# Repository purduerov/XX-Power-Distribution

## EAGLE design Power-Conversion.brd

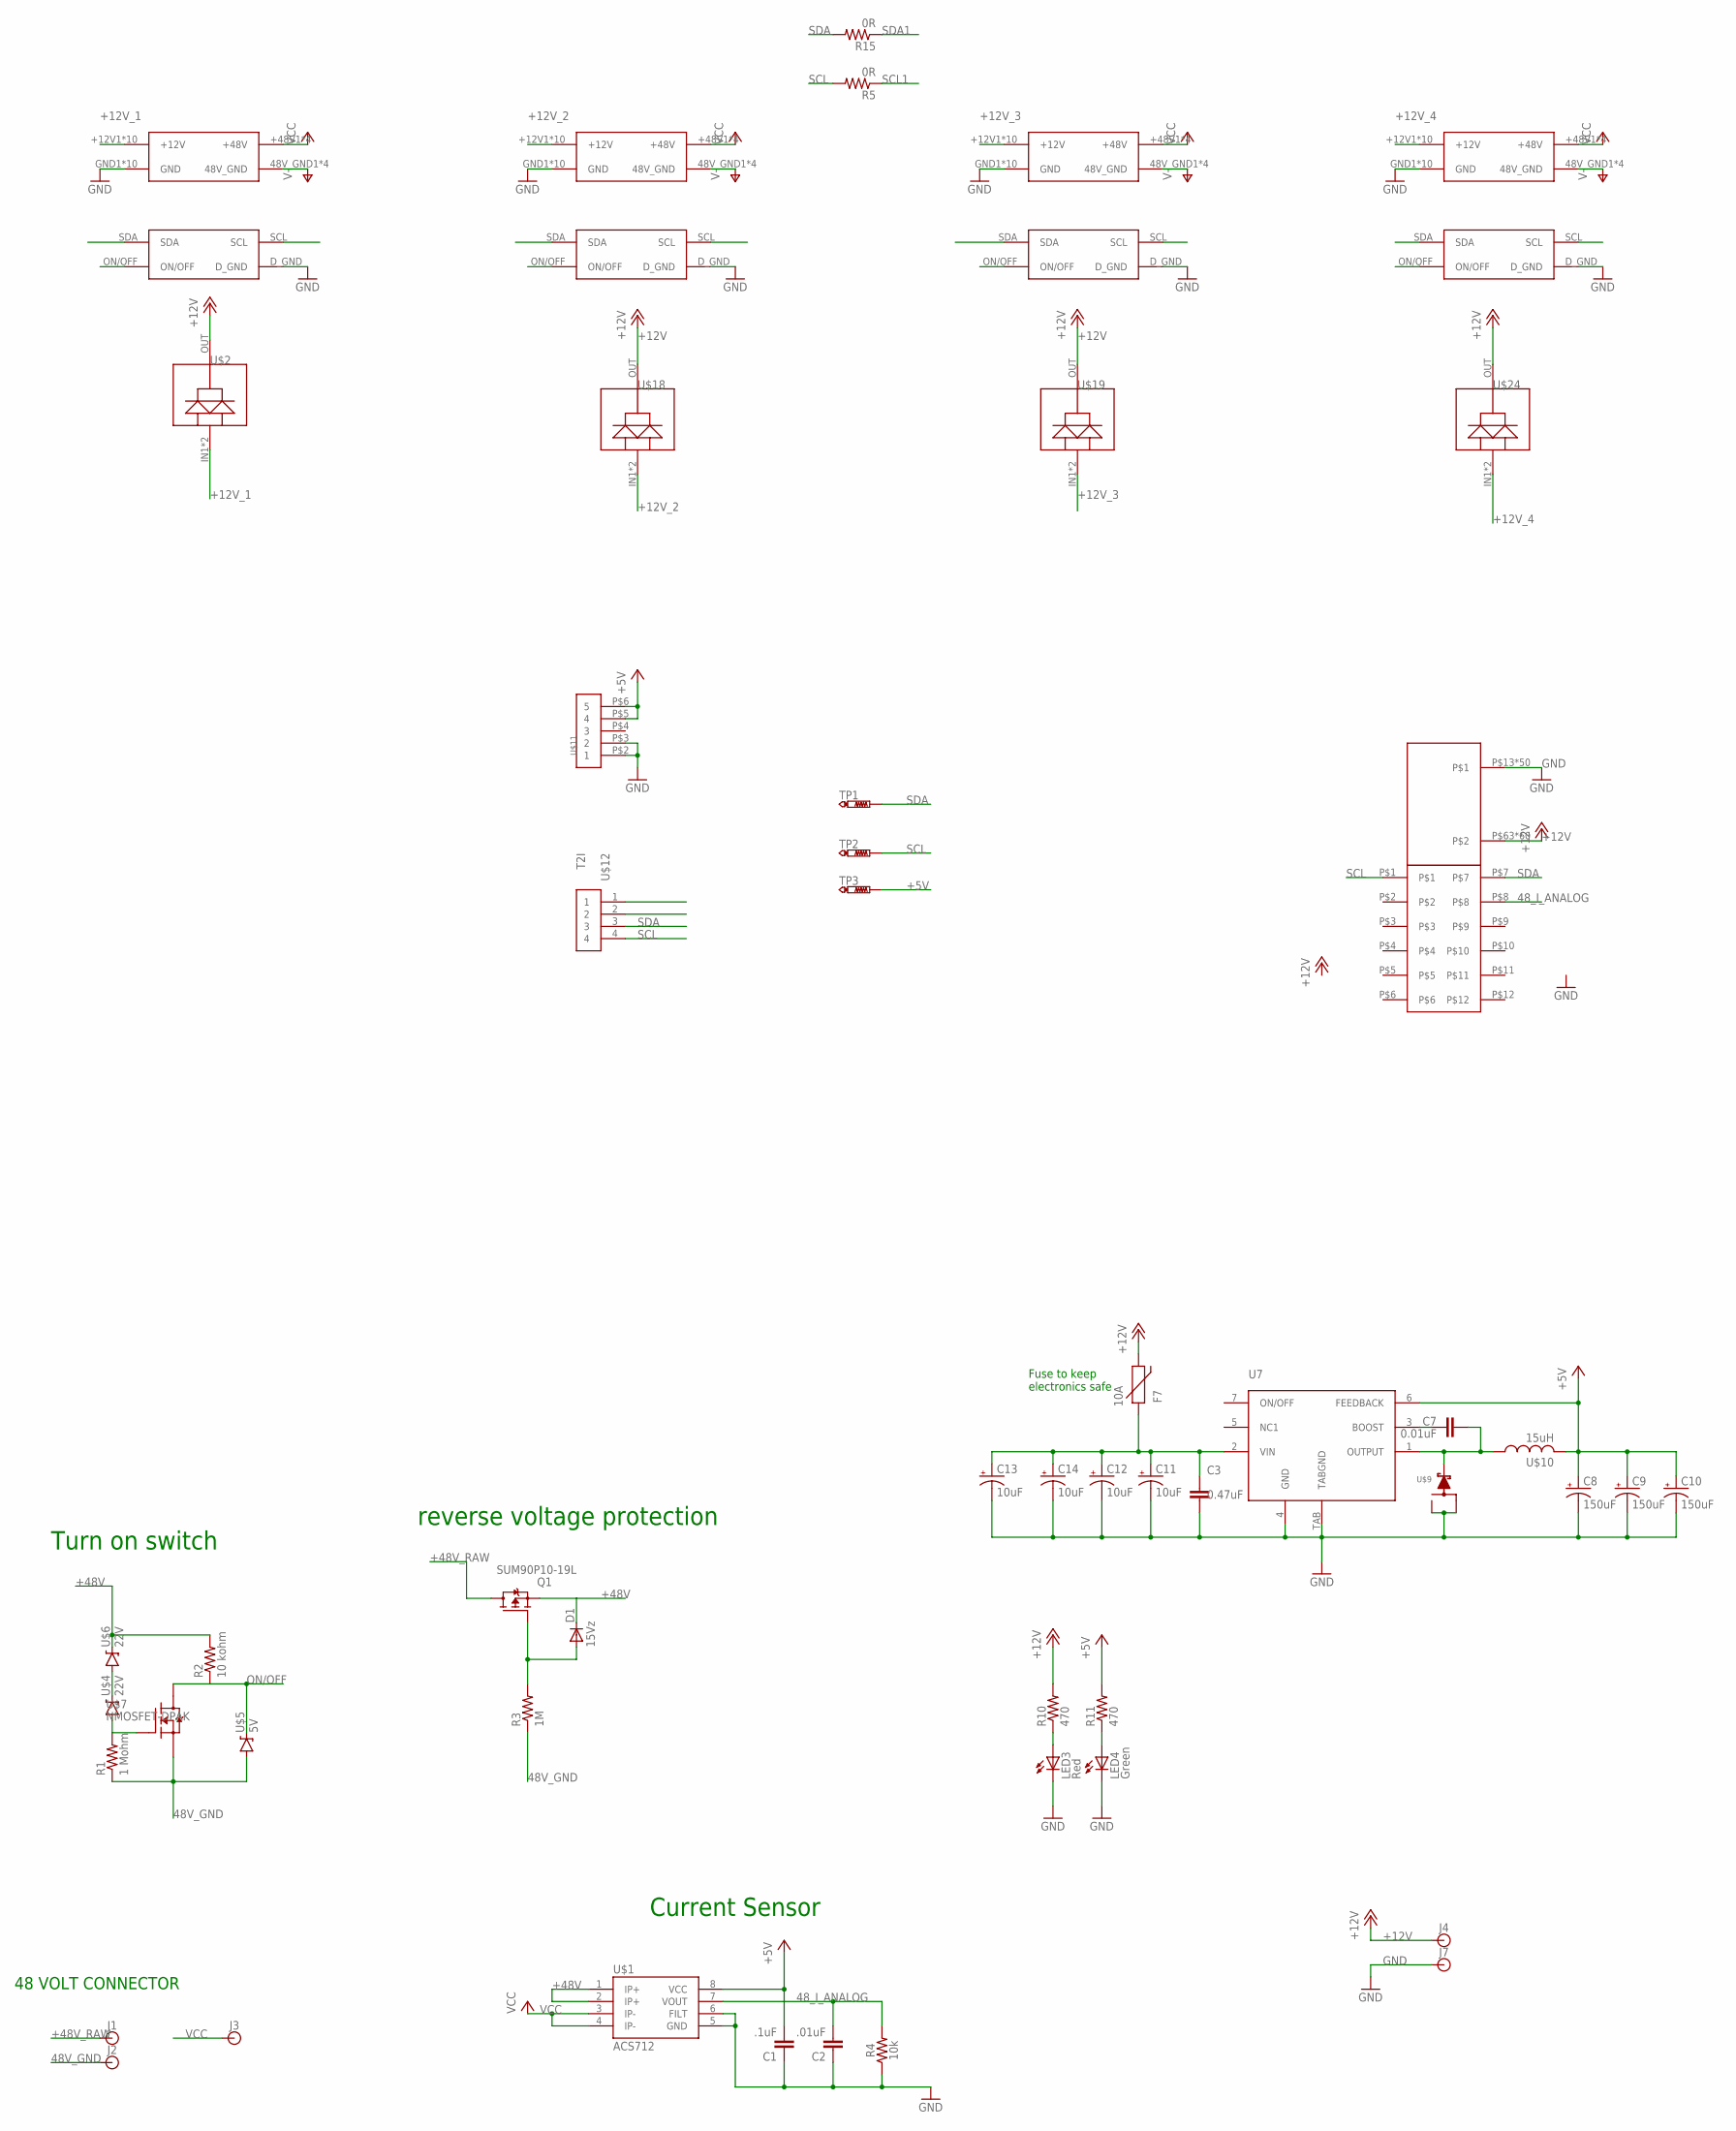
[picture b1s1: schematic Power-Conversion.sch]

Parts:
C1: .1uF; 0603
C2: .01uF; 0603
C3: 0.47uF; C0603
C7: 0.01uF; 0603-CAP
C8, C9, C10: 150uF; CTAN(7.30_4.30MM)
C11, C12, C13, C14: 10uF; CTAN(7.30_4.30MM)
D1: 15Vz; SOD123; PARTNO MMSZ5245BFSCT-ND
F7: 10A; PTC-2920
J1, J2, J3, J4, J7: BANANA_CONN
LED3: Red; LED-0603
LED4: Green; LED-0603
Q1: SUM90P10-19L; TO263; PARTNO SUM90P10-19L-E3CT-ND
R1: 1 Mohm; 0603-RES
R2: 10 kohm; 0603-RES
R3: 1M; R0603; PARTNO 1.00MHCT-ND
R4: 10k; 0603
R5, R15: 0R; R0603
R10, R11: 470; R0603
TP1, TP2, TP3: PTR1PAD1-13; P1-13
U7: LM2678
U$1: ACS712; SO08
U$2, U$18, U$19, U$24: DIODE
U$4, U$6: 22V; SOT23-3
U$5: 5V; SOT23-3
U$7: NMOSFET-DPAK; DPAK
U$8: ESC-FULL
U$9: SWITCHMODE_SCHOTTKY; DPAK-3
U$10: 15uH; HCMA1305
U$11: T2I5P
U$12: T2I
U$20, U$21, U$22, U$23: BRICK_TO_POWER_DIST_WHOLE

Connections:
48V_GND: J2.P$1, R1.1, R3.1, U$5.1 (A), U$7.3 (S), U$20.48V_GND1 (48V_GND), U$20.48V_GND2 (48V_GND), U$20.48V_GND3 (48V_GND), U$20.48V_GND4 (48V_GND), U$21.48V_GND1 (48V_GND), U$21.48V_GND2 (48V_GND), U$21.48V_GND3 (48V_GND), U$21.48V_GND4 (48V_GND), U$22.48V_GND1 (48V_GND), U$22.48V_GND2 (48V_GND), U$22.48V_GND3 (48V_GND), U$22.48V_GND4 (48V_GND), U$23.48V_GND1 (48V_GND), U$23.48V_GND2 (48V_GND), U$23.48V_GND3 (48V_GND), U$23.48V_GND4 (48V_GND)
48_I_ANALOG: C2.2, R4.2, U$1.7 (VOUT), U$8.P$8
+5V: C1.2, C8.+, C9.+, C10.+, R11.2, TP3.TP, U7.6 (FEEDBACK), U$1.8 (VCC), U$10.P$2 (2), U$11.P$5 (4), U$11.P$6 (5)
+12V: F7.2, J4.P$1, R10.2, U$2.OUT, U$8.P$63, U$8.P$64, U$8.P$65, U$8.P$66, U$8.P$67, U$8.P$68, U$8.P$69, U$8.P$70, U$8.P$71, U$8.P$72, U$8.P$73, U$8.P$74, U$8.P$75, U$8.P$76, U$8.P$77, U$8.P$78, U$8.P$79, U$8.P$80, U$8.P$81, U$8.P$82, U$8.P$83, U$8.P$84, U$8.P$85, U$8.P$86, U$8.P$87, U$8.P$88, U$8.P$89, U$8.P$90, U$8.P$91, U$8.P$92, U$8.P$101, U$8.P$102, U$8.P$103, U$8.P$104, U$8.P$105, U$8.P$106, U$8.P$107, U$8.P$108, U$8.P$109, U$8.P$110, U$8.P$111, U$8.P$112, U$8.P$113, U$8.P$114, U$8.P$115, U$8.P$116, U$8.P$117, U$8.P$118, U$8.P$119, U$8.P$120, U$8.P$121, U$8.P$122, U$8.P$123, U$8.P$124, U$8.P$125, U$8.P$126, U$8.P$127, U$8.P$128, U$8.P$129, U$8.P$130, U$18.OUT, U$19.OUT, U$24.OUT
+12V_1: U$2.IN1 (IN2), U$2.IN2, U$20.+12V1 (+12V), U$20.+12V2 (+12V), U$20.+12V3 (+12V), U$20.+12V4 (+12V), U$20.+12V5 (+12V), U$20.+12V6 (+12V), U$20.+12V7 (+12V), U$20.+12V8 (+12V), U$20.+12V9 (+12V), U$20.+12V10 (+12V)
+12V_2: U$18.IN1 (IN2), U$18.IN2, U$21.+12V1 (+12V), U$21.+12V2 (+12V), U$21.+12V3 (+12V), U$21.+12V4 (+12V), U$21.+12V5 (+12V), U$21.+12V6 (+12V), U$21.+12V7 (+12V), U$21.+12V8 (+12V), U$21.+12V9 (+12V), U$21.+12V10 (+12V)
+12V_3: U$19.IN1 (IN2), U$19.IN2, U$22.+12V1 (+12V), U$22.+12V2 (+12V), U$22.+12V3 (+12V), U$22.+12V4 (+12V), U$22.+12V5 (+12V), U$22.+12V6 (+12V), U$22.+12V7 (+12V), U$22.+12V8 (+12V), U$22.+12V9 (+12V), U$22.+12V10 (+12V)
+12V_4: U$23.+12V1 (+12V), U$23.+12V2 (+12V), U$23.+12V3 (+12V), U$23.+12V4 (+12V), U$23.+12V5 (+12V), U$23.+12V6 (+12V), U$23.+12V7 (+12V), U$23.+12V8 (+12V), U$23.+12V9 (+12V), U$23.+12V10 (+12V), U$24.IN1 (IN2), U$24.IN2
+48V: D1.C, Q1.2 (S), R2.2, U$1.1 (IP+), U$1.2 (IP+), U$6.3 (C)
+48V_RAW: J1.P$1, Q1.3 (D)
GND: C1.1, C2.1, C3.2, C8.-, C9.-, C10.-, C11.-, C12.-, C13.-, C14.-, J7.P$1, LED3.C, LED4.C, R4.1, U7.4 (GND), U7.TAB (TABGND), U$1.5 (GND), U$1.6 (FILT), U$8.P$13, U$8.P$14, U$8.P$15, U$8.P$16, U$8.P$17, U$8.P$18, U$8.P$19, U$8.P$20, U$8.P$21, U$8.P$22, U$8.P$23, U$8.P$24, U$8.P$25, U$8.P$26, U$8.P$27, U$8.P$28, U$8.P$29, U$8.P$30, U$8.P$31, U$8.P$32, U$8.P$33, U$8.P$34, U$8.P$35, U$8.P$36, U$8.P$37, U$8.P$38, U$8.P$39, U$8.P$40, U$8.P$41, U$8.P$42, U$8.P$43, U$8.P$44, U$8.P$45, U$8.P$46, U$8.P$47, U$8.P$48, U$8.P$49, U$8.P$50, U$8.P$51, U$8.P$52, U$8.P$53, U$8.P$54, U$8.P$55, U$8.P$56, U$8.P$57, U$8.P$58, U$8.P$59, U$8.P$60, U$8.P$61, U$8.P$62, U$9.P$1, U$9.P$3, U$11.P$2 (1), U$11.P$3 (2), U$20.D_GND, U$20.GND1 (GND), U$20.GND2 (GND), U$20.GND3 (GND), U$20.GND4 (GND), U$20.GND5 (GND), U$20.GND6 (GND), U$20.GND7 (GND), U$20.GND8 (GND), U$20.GND9 (GND), U$20.GND10 (GND), U$21.D_GND, U$21.GND1 (GND), U$21.GND2 (GND), U$21.GND3 (GND), U$21.GND4 (GND), U$21.GND5 (GND), U$21.GND6 (GND), U$21.GND7 (GND), U$21.GND8 (GND), U$21.GND9 (GND), U$21.GND10 (GND), U$22.D_GND, U$22.GND1 (GND), U$22.GND2 (GND), U$22.GND3 (GND), U$22.GND4 (GND), U$22.GND5 (GND), U$22.GND6 (GND), U$22.GND7 (GND), U$22.GND8 (GND), U$22.GND9 (GND), U$22.GND10 (GND), U$23.D_GND, U$23.GND1 (GND), U$23.GND2 (GND), U$23.GND3 (GND), U$23.GND4 (GND), U$23.GND5 (GND), U$23.GND6 (GND), U$23.GND7 (GND), U$23.GND8 (GND), U$23.GND9 (GND), U$23.GND10 (GND)
unnamed: C3.1, C11.+, C12.+, C13.+, C14.+, F7.1, U7.2 (VIN)
unnamed: D1.A, Q1.1 (G), R3.2
unnamed: U$4.3 (C), U$6.1 (A)
unnamed: R1.2, U$4.1 (A), U$7.1 (G)
unnamed: C7.1, U7.3 (BOOST)
unnamed: C7.2, U7.1 (OUTPUT), U$9.P$4, U$10.P$1 (1)
unnamed: LED3.A, R10.1
unnamed: LED4.A, R11.1
ON/OFF: R2.1, U$5.3 (C), U$7.4 (D1), U$20.ON/OFF, U$21.ON/OFF, U$22.ON/OFF, U$23.ON/OFF
SCL: R5.2, TP2.TP, U$8.P$1, U$12.4
SCL1: R5.1, U$20.SCL, U$21.SCL, U$22.SCL, U$23.SCL
SDA: R15.2, TP1.TP, U$8.P$7, U$12.3
SDA1: R15.1, U$20.SDA, U$21.SDA, U$22.SDA, U$23.SDA
VCC: J3.P$1, U$1.3 (IP-), U$1.4 (IP-), U$20.+48V1 (+48V), U$20.+48V2 (+48V), U$20.+48V3 (+48V), U$20.+48V4 (+48V), U$21.+48V1 (+48V), U$21.+48V2 (+48V), U$21.+48V3 (+48V), U$21.+48V4 (+48V), U$22.+48V1 (+48V), U$22.+48V2 (+48V), U$22.+48V3 (+48V), U$22.+48V4 (+48V), U$23.+48V1 (+48V), U$23.+48V2 (+48V), U$23.+48V3 (+48V), U$23.+48V4 (+48V)

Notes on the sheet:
Turn on switch
reverse voltage protection
48 VOLT CONNECTOR
Current Sensor
Fuse to keep electronics safe

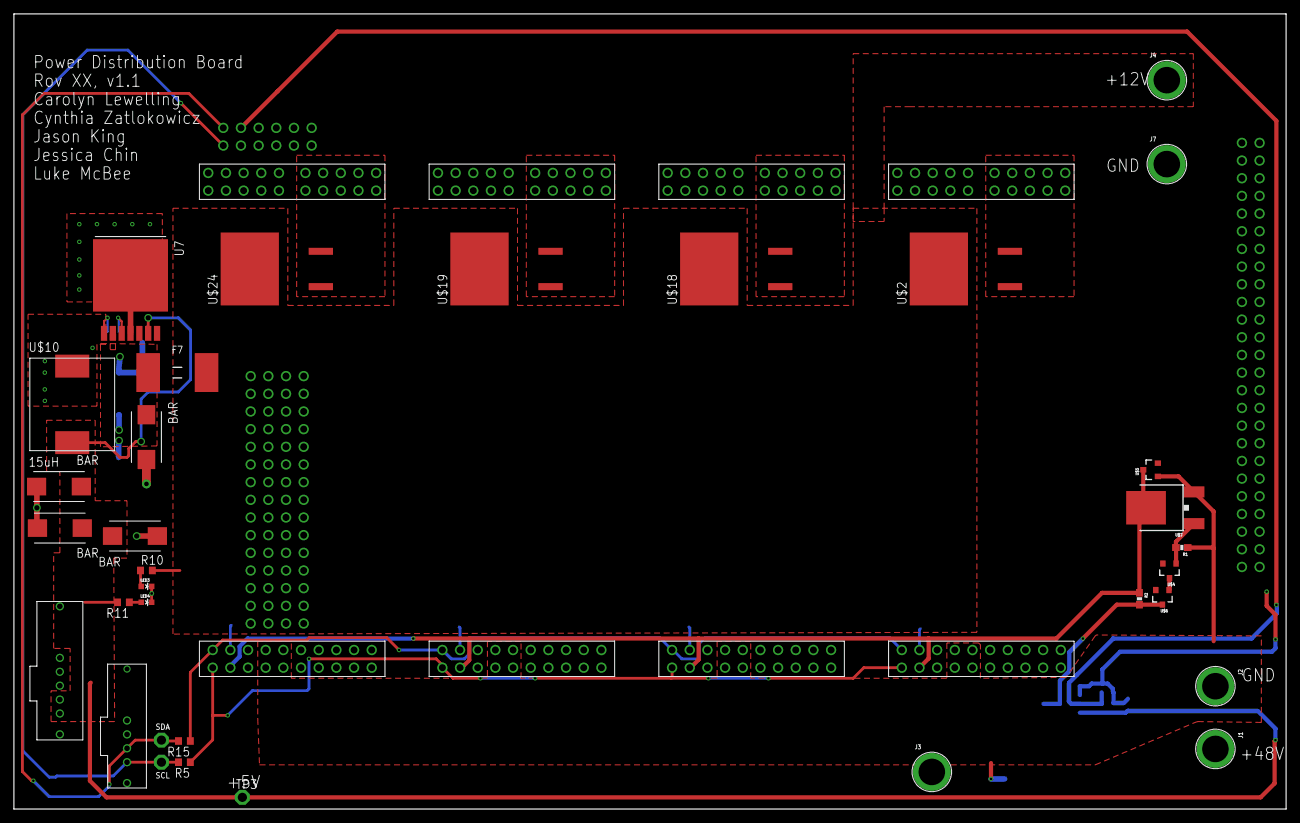
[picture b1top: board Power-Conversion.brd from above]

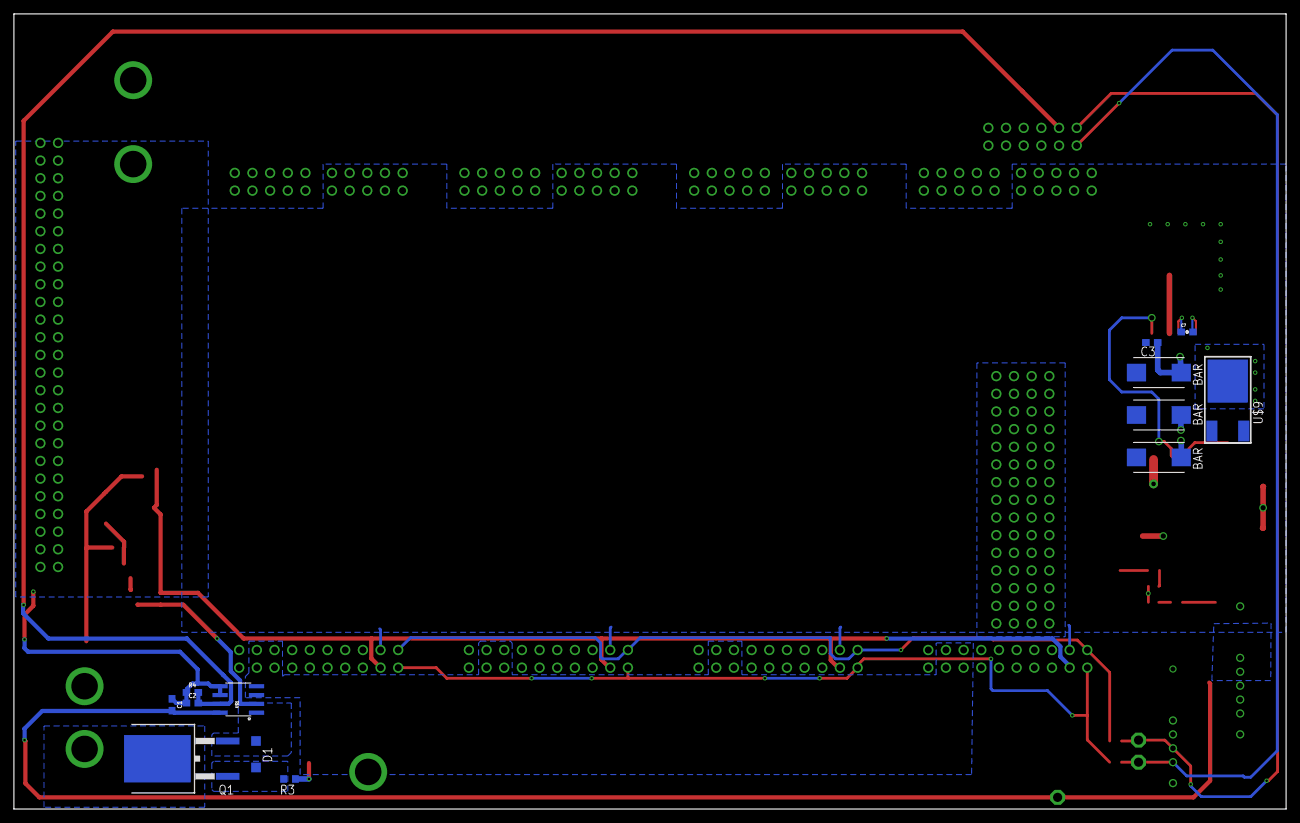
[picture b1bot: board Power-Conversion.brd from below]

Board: 2 copper layers, 182.9 x 114.3 mm, 52 parts (13 on the bottom side), 25 nets.

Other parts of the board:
U$15: POWER_DIST_TO_ESC

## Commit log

2017-09-28 initial
2017-10-03 getting rid of old layout
2017-10-14 Added buck converter, reverse voltage protection, and turn on switch
2017-10-15 Added gitignore
2017-10-15 Removed unnecessary temp files
2017-10-28 added current sense
    added current sense and support things
2017-11-02 Added voltage connectors
    added the voltage connectors
2017-11-10 added Connectors
    added connectors to schematic
2017-11-11 Added micro
    added the microcontroller.
2017-11-11 Added Connectors
2017-11-11 Removed micro
    removed micro controller and added capacitors to linear regelator
2017-11-17 Connected the connectors
2017-11-17 Started Board layout
2017-12-01 Fix Board Layout
2017-12-01 Routed Board
    Added Diodes
2017-12-27 Added new connectors for 8th bricks
2017-12-30 Initial layout of parts has begun. Still need to reduce down the size a lot...
2017-12-30 Shrinking down the board more and figuring out part placement
2018-01-01 Finalizing intial layout of parts
2018-01-01 Moved around parts to near final postions. Next comes routing.
2018-01-01 Added fuse to 12V going to rasp pi
2018-01-02 Got buck regulator done
2018-01-02 Added standard ESC board connector
2018-01-02 Some routing done
2018-01-08 finished board layout
    first draft board layout
2018-01-08 Added new ESC to power distribution board part
2018-01-08 Fixed to work with new connector part
2018-01-08 Added silkscreen
2018-01-08 Stuff
2018-01-08 Fixed trace widths for +48V and GND
2018-01-08 Cleaning up
2018-01-10 Version submitted to elecrow
2018-01-31 Put in resistor values on ON/OFF switch
    on ON/OFF switch
2018-02-13 Some changes for second round of manufacturing
2018-02-13 Added isolation for every pour, fixed issue with inductor and fuse overlap, and labeled tantalum capacitors.
2018-02-15 changed kirby, version number, and erc issue
    Changed silkscreen & weird erc issue with J1 and J2
2018-02-15 Added +5V test point, removed text from Kirby, modified connector to RPi so Power and GND dont overlap

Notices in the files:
parts and their libraries:
SparkFun-Capacitors: Licensing: Creative Commons ShareAlike 4.0 International - https://creativecommons.org/licenses/by-sa/4.0
